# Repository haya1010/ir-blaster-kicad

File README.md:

# M5 / ESP32 High-Power IR Blaster — Rev A

M5 Atom または ESP32 から家電を操作するための、赤外線送受信ボードです。
既存の `m5-ir-remote-studio` の初期設定に合わせ、送信は GPIO26、受信は GPIO32 を想定しています。

## できること

- 940 nm 高出力IR LEDを3灯同時にパルス駆動
- AO3400A MOSFETでESP32のGPIOを保護
- TSOP38238（38 kHz）でリモコン信号を受信
- 受信部を3.3 Vで動かし、ESP32入力へ安全な電圧で返す
- TX動作確認用の可視LED
- JST-PH 4ピンでM5 Atom／ESP32へ接続
- 52 × 40 mm、M3穴4個

## 接続

| J1 pin | 信号 | M5 Atom / ESP32 |
|---|---|---|
| 1 | IR_TX | GPIO26 |
| 2 | IR_RX | GPIO32 |
| 3 | +5V | 5V |
| 4 | GND | GND |

J1のシルク面表記は左から `TX / RX / 5V / GND` です。Groveケーブルは製品により信号線の割り当てが異なるため、色だけで判断せず導通を確認してください。

## 電気的な目安

IR LED 1灯あたりのピーク電流は、5 V、順方向電圧約1.35 V、33 Ωとして約111 mAです。
3灯合計は送信パルス中に約333 mAとなります。38 kHz変調かつ短いリモコン送信を前提としています。

連続点灯はしないでください。IR LEDにはパルス定格に余裕のある部品（TSAL6200相当）を使い、R3〜R5はパルス負荷に耐える0.5 W品を推奨します。

## KiCadで開く

`m5_ir_blaster.kicad_pro` または `m5_ir_blaster.kicad_pcb` を開いてください。
フットプリントはPCBファイル内に埋め込んであるため、追加ライブラリは不要です。

## JLCPCBで基板だけ注文する

アップロードするファイルは `manufacturing/m5_ir_blaster_revA_gerbers.zip` です。
KiCadプロジェクトZIPではなく、Gerber ZIPの方を使ってください。

推奨する初回設定:

| 項目 | 設定 |
|---|---|
| Base Material | FR-4 |
| Layers | 2 |
| Dimensions | 52 × 40 mm（自動認識を確認） |
| PCB Qty | 5 |
| Thickness | 1.6 mm |
| Copper Weight | 1 oz |
| PCB Color | Green（好みで変更可） |
| Silkscreen | White |
| Surface Finish | LeadFree HASL |
| Via Covering | Tented |
| Remove Order Number | 見た目優先なら Yes |
| PCB Assembly | No（部品は手はんだ） |

アップロード後のGerber Viewerで、外形、M3穴4個、IR LED穴3組、J1の4ピン穴、表面シルクを確認してください。

## 製造前の確認

これは試作Rev Aです。発注前に次を確認してください。

1. 使用するJSTコネクタの実物とピン順
2. 選んだIR LEDの極性と最大パルス電流
3. TSOP38238互換品のピン配列（OUT / GND / VS）
4. KiCadのDRC
5. 実機の5 V供給能力

## データシート確認済みの要点

- MCP1700 SOT-23: 1=GND、2=VOUT、3=VIN
- TSOP38238: 1=OUT、2=GND、3=VS
- TSAL6200: 940 nm、連続100 mA、規定条件でピーク200 mA
- AO3400A: 2.5 Vゲート駆動時のオン抵抗が規定されたロジックレベルMOSFET

メーカー資料:

- https://www.microchip.com/en-us/product/mcp1700
- https://www.vishay.com/docs/82491/tsop382.pdf
- https://www.vishay.com/docs/81010/tsal6200.pdf
- https://www.aosmd.com/products/mosfets/low-voltage-mosfets-12v-30v/ao3400a

## ファームウェア

既存スケッチの設定をそのまま使用できます。

```cpp
static const uint16_t IR_RX_PIN = 32;
static const uint16_t IR_TX_PIN = 26;
```

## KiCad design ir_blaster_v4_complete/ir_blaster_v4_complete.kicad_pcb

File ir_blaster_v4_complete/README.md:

# IR Blaster HW V1.0 — REV4 complete

ESP32-WROOM-32E-N16、USB-C 5V入力、12灯IR送信、IR受信、操作ボタン、
試作用1x6書き込み端子、量産用2x3ポゴパッドを載せた直径78 mmの完成基板です。

標準の発注構成は **Hybrid PCBA** です。JLCPCBにはSMT部品だけを実装してもらい、
D1–D12、U_RX、C_BULK、J_PROGはDNP（未実装）にします。これらは後から手はんだします。

## そのまま使う発注ファイル

- `manufacturing/ir_blaster_v4_complete_gerbers.zip`
- `assembly/BOM_JLCPCB.csv`
- `assembly/CPL_JLCPCB.csv`
- 一括確認用 `release/ir_blaster_v4_complete_order_bundle.zip`
- 組立図 `docs/ir_blaster_v4_complete_assembly_drawing.pdf`
- 組立注記 `docs/ASSEMBLY_DRAWING.md`

## 検査結果

- KiCad 9 ERC: blocking error 0
- KiCad 9 DRC: blocking error 0 / unconnected 0
- 2層、FR-4、1.6 mm、1 oz、外形78 x 78 mm
- USB-Cは5 V給電専用。データ線は未接続、CC1/CC2は各5.1 kΩでGNDへ接続
- JLCPCB Gerber Viewerで2層・78 x 78 mmとして解析済み（2026-08-16）

発注操作の直前に `docs/PRE_ORDER_CHECKLIST.md` とJLCPCBの部品向きプレビューを確認してください。

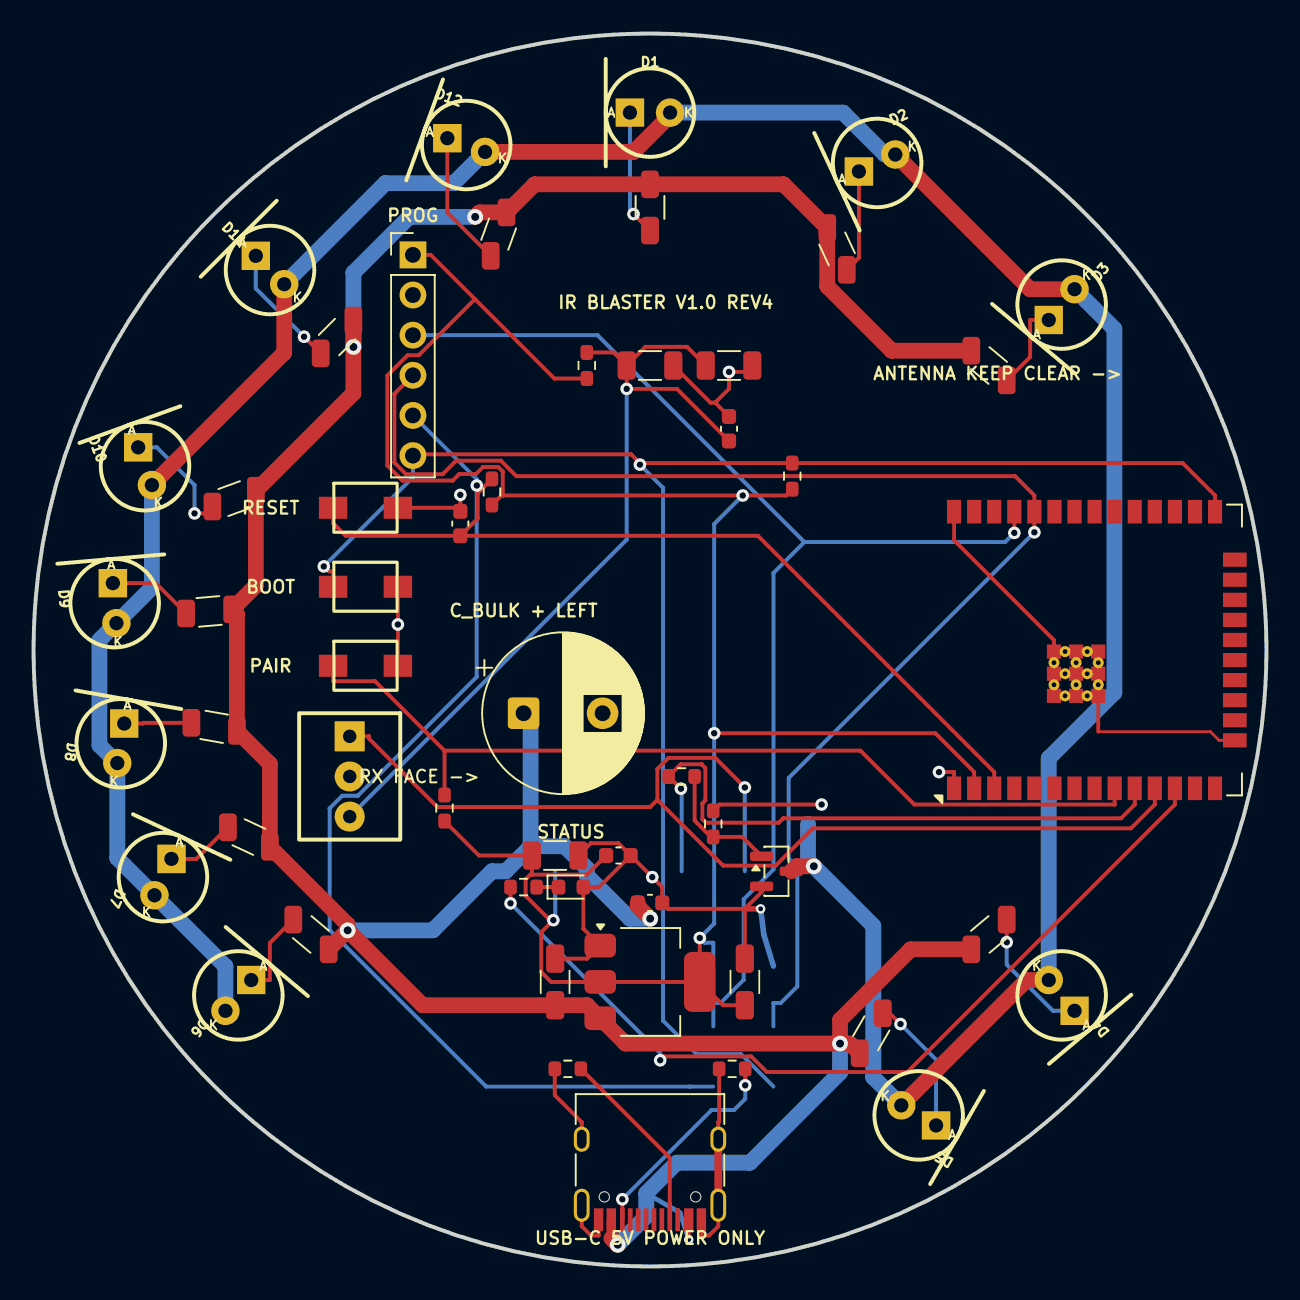
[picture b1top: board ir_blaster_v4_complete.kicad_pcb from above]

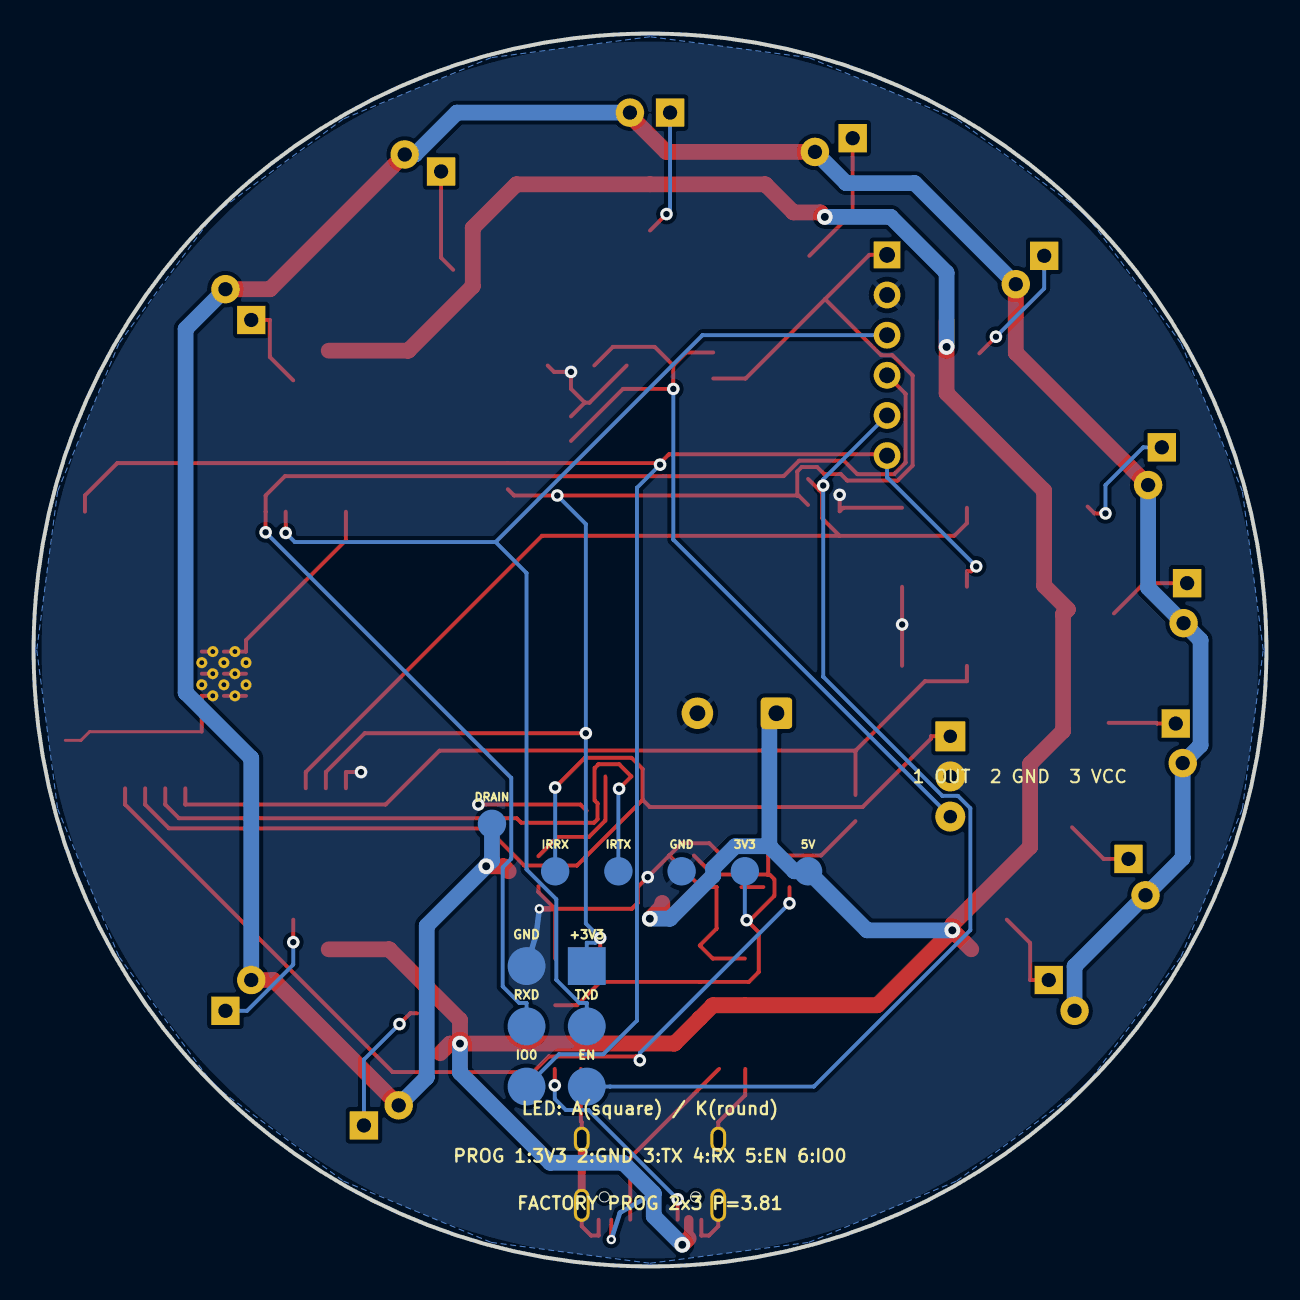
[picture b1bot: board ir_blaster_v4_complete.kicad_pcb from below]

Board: 2 copper layers, 78.0 x 78.0 mm, 65 parts (12 on the bottom side), 29 nets.

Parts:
C1, C2, C4: 22uF; C_1206_3216Metric
C3, C5: 100nF; C_0603_1608Metric
C_BULK: 1000uF 10V DNP; CP_Radial_D10.0mm_P5.00mm
C_EN: 1uF; C_0603_1608Metric
C_RX1, C_RX2: 22uF; C_1206_3216Metric
C_RX3: 100nF; C_0603_1608Metric
D1, D4, D7, D10: OSI5LA7WA1B_WIDE_DNP; IR_LED_5mm_Universal_P2.54
D2, D3, D5, D6, D8, D9, D11, D12: OSI5LA5A33A-B_NARROW_DNP; IR_LED_5mm_Universal_P2.54
D_STATUS: RED; LED_0603_1608Metric
J1: USB-C 5V POWER ONLY; USB_C_Receptacle_HRO_TYPE-C-31-M-12
J_PROG: 1x6 2.54mm DNP; PinHeader_1x06_P2.54mm_Vertical
Q1: AO3400A; SOT-23
R1, R2, R3, R4, R5, R6, R7, R8, R9, R10, R11, R12: 100R 0.25W; R_1206_3216Metric
R_BOOT: 10k; R_0603_1608Metric
R_CC1, R_CC2: 5.1k; R_0603_1608Metric
R_EN: 10k; R_0603_1608Metric
R_GATE: 220R; R_0603_1608Metric
R_PAIR: 10k; R_0603_1608Metric
R_PD: 10k; R_0603_1608Metric
R_RX: 100R; R_0603_1608Metric
R_STATUS: 1k; R_0603_1608Metric
SW_BOOT: TS-1088R-02026
SW_PAIR: TS-1088R-02026
SW_RESET: TS-1088R-02026
TP_3V3: 3V3; TestPad_D1.8
TP_5V: 5V; TestPad_D1.8
TP_DRAIN: DRAIN; TestPad_D1.8
TP_GND: GND; TestPad_D1.8
TP_PROG_3V3: +3V3; PogoPad_D2.4
TP_PROG_EN: EN; PogoPad_D2.4
TP_PROG_GND: GND; PogoPad_D2.4
TP_PROG_IO0: IO0; PogoPad_D2.4
TP_PROG_RXD: RXD; PogoPad_D2.4
TP_PROG_TXD: TXD; PogoPad_D2.4
TP_RX: IRRX; TestPad_D1.8
TP_TX: IRTX; TestPad_D1.8
U1: ESP32-WROOM-32E-N16; ESP32-WROOM-32E
U2: AMS1117-3.3; SOT-223-3_TabPin2
U_RX: OSRB38C9AA_DNP; OSRB38C9AA

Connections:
+3V3: C2.1, C4.1, C5.1, J_PROG.1, R_BOOT.1, R_EN.1, R_PAIR.1, R_RX.1, TP_3V3.1, TP_PROG_3V3.1, U1.2, U2.2
+5V: C1.1, C3.1, C_BULK.1, J1.A4, J1.A9, J1.B4, J1.B9, R1.1, R2.1, R3.1, R4.1, R5.1, R6.1, R7.1, R8.1, R9.1, R10.1, R11.1, R12.1, TP_5V.1, U2.3
CC1: J1.A5, R_CC1.1
CC2: J1.B5, R_CC2.1
EN: C_EN.1, J_PROG.5, R_EN.2, SW_RESET.1, TP_PROG_EN.1, U1.3
GND: C1.2, C2.2, C3.2, C4.2, C5.2, C_BULK.2, C_EN.2, C_RX1.2, C_RX2.2, C_RX3.2, D_STATUS.2, J1.A1, J1.A12, J1.B1, J1.B12, J1.S1, J_PROG.2, Q1.2, R_CC1.2, R_CC2.2, R_PD.2, SW_BOOT.2, SW_PAIR.2, SW_RESET.2, TP_GND.1, TP_PROG_GND.1, U1.1, U1.15, U1.38, U1.39, U2.1, U_RX.2
IO0: J_PROG.6, R_BOOT.2, SW_BOOT.1, TP_PROG_IO0.1, U1.25
IR_RX: TP_RX.1, U1.11, U_RX.1
IR_RX_VCC: C_RX1.1, C_RX2.1, C_RX3.1, R_RX.2, U_RX.3
IR_TX: R_GATE.1, TP_TX.1, U1.10
LED_A1: D1.1, R1.2
LED_A2: D2.1, R2.2
LED_A3: D3.1, R3.2
LED_A4: D4.1, R4.2
LED_A5: D5.1, R5.2
LED_A6: D6.1, R6.2
LED_A7: D7.1, R7.2
LED_A8: D8.1, R8.2
LED_A9: D9.1, R9.2
LED_A10: D10.1, R10.2
LED_A11: D11.1, R11.2
LED_A12: D12.1, R12.2
LED_DRAIN: D1.2, D2.2, D3.2, D4.2, D5.2, D6.2, D7.2, D8.2, D9.2, D10.2, D11.2, D12.2, Q1.3, TP_DRAIN.1
MOS_GATE: Q1.1, R_GATE.2, R_PD.1
PAIR: R_PAIR.2, SW_PAIR.1, U1.9
STATUS: R_STATUS.1, U1.12
STATUS_LED: D_STATUS.1, R_STATUS.2
U0RXD: J_PROG.4, TP_PROG_RXD.1, U1.34
U0TXD: J_PROG.3, TP_PROG_TXD.1, U1.35

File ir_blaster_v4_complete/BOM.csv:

Reference,Qty,Value,Footprint,Manufacturer,MPN,JLC/LCSC,Assembly,Notes
D1,1,OSI5LA7WA1B_WIDE_DNP,IR_LED_5mm_Universal_P2.54,OptoSupply,OSI5LA7WA1B,DNP,DNP / hand solder,Tilt 30-45 degrees outward by hand
R1,1,100R 0.25W,R_1206_3216Metric,UNI-ROYAL,1206W4F1000T5E,C17901,SMT,
D2,1,OSI5LA5A33A-B_NARROW_DNP,IR_LED_5mm_Universal_P2.54,OptoSupply,OSI5LA5A33A-B,DNP,DNP / hand solder,Tilt 30-45 degrees outward by hand
R2,1,100R 0.25W,R_1206_3216Metric,UNI-ROYAL,1206W4F1000T5E,C17901,SMT,
D3,1,OSI5LA5A33A-B_NARROW_DNP,IR_LED_5mm_Universal_P2.54,OptoSupply,OSI5LA5A33A-B,DNP,DNP / hand solder,Tilt 30-45 degrees outward by hand
R3,1,100R 0.25W,R_1206_3216Metric,UNI-ROYAL,1206W4F1000T5E,C17901,SMT,
D4,1,OSI5LA7WA1B_WIDE_DNP,IR_LED_5mm_Universal_P2.54,OptoSupply,OSI5LA7WA1B,DNP,DNP / hand solder,Tilt 30-45 degrees outward by hand
R4,1,100R 0.25W,R_1206_3216Metric,UNI-ROYAL,1206W4F1000T5E,C17901,SMT,
D5,1,OSI5LA5A33A-B_NARROW_DNP,IR_LED_5mm_Universal_P2.54,OptoSupply,OSI5LA5A33A-B,DNP,DNP / hand solder,Tilt 30-45 degrees outward by hand
R5,1,100R 0.25W,R_1206_3216Metric,UNI-ROYAL,1206W4F1000T5E,C17901,SMT,
D6,1,OSI5LA5A33A-B_NARROW_DNP,IR_LED_5mm_Universal_P2.54,OptoSupply,OSI5LA5A33A-B,DNP,DNP / hand solder,Tilt 30-45 degrees outward by hand
R6,1,100R 0.25W,R_1206_3216Metric,UNI-ROYAL,1206W4F1000T5E,C17901,SMT,
D7,1,OSI5LA7WA1B_WIDE_DNP,IR_LED_5mm_Universal_P2.54,OptoSupply,OSI5LA7WA1B,DNP,DNP / hand solder,Tilt 30-45 degrees outward by hand
R7,1,100R 0.25W,R_1206_3216Metric,UNI-ROYAL,1206W4F1000T5E,C17901,SMT,
D8,1,OSI5LA5A33A-B_NARROW_DNP,IR_LED_5mm_Universal_P2.54,OptoSupply,OSI5LA5A33A-B,DNP,DNP / hand solder,Tilt 30-45 degrees outward by hand
R8,1,100R 0.25W,R_1206_3216Metric,UNI-ROYAL,1206W4F1000T5E,C17901,SMT,
D9,1,OSI5LA5A33A-B_NARROW_DNP,IR_LED_5mm_Universal_P2.54,OptoSupply,OSI5LA5A33A-B,DNP,DNP / hand solder,Tilt 30-45 degrees outward by hand
R9,1,100R 0.25W,R_1206_3216Metric,UNI-ROYAL,1206W4F1000T5E,C17901,SMT,
D10,1,OSI5LA7WA1B_WIDE_DNP,IR_LED_5mm_Universal_P2.54,OptoSupply,OSI5LA7WA1B,DNP,DNP / hand solder,Tilt 30-45 degrees outward by hand
R10,1,100R 0.25W,R_1206_3216Metric,UNI-ROYAL,1206W4F1000T5E,C17901,SMT,
D11,1,OSI5LA5A33A-B_NARROW_DNP,IR_LED_5mm_Universal_P2.54,OptoSupply,OSI5LA5A33A-B,DNP,DNP / hand solder,Tilt 30-45 degrees outward by hand
R11,1,100R 0.25W,R_1206_3216Metric,UNI-ROYAL,1206W4F1000T5E,C17901,SMT,
D12,1,OSI5LA5A33A-B_NARROW_DNP,IR_LED_5mm_Universal_P2.54,OptoSupply,OSI5LA5A33A-B,DNP,DNP / hand solder,Tilt 30-45 degrees outward by hand
R12,1,100R 0.25W,R_1206_3216Metric,UNI-ROYAL,1206W4F1000T5E,C17901,SMT,
U1,1,ESP32-WROOM-32E-N16,ESP32-WROOM-32E,Espressif Systems,ESP32-WROOM-32E-N16,C701343,SMT,16MB flash; Standard PCBA; X-ray required
J1,1,USB-C 5V POWER ONLY,USB_C_Receptacle_HRO_TYPE-C-31-M-12,Korean Hroparts Elec,TYPE-C-31-M-12,C165948,SMT,
U2,1,AMS1117-3.3,SOT-223-3_TabPin2,Advanced Monolithic Systems,AMS1117-3.3,C6186,SMT,1A LDO; large copper area required
C1,1,22uF,C_1206_3216Metric,Samsung Electro-Mechanics,CL31A226KAHNNNE,C12891,SMT,
C2,1,22uF,C_1206_3216Metric,Samsung Electro-Mechanics,CL31A226KAHNNNE,C12891,SMT,
C3,1,100nF,C_0603_1608Metric,Samsung Electro-Mechanics,CL10B104KB8NNNC,C1591,SMT,
C4,1,22uF,C_1206_3216Metric,Samsung Electro-Mechanics,CL31A226KAHNNNE,C12891,SMT,
C5,1,100nF,C_0603_1608Metric,Samsung Electro-Mechanics,CL10B104KB8NNNC,C1591,SMT,
R_EN,1,10k,R_0603_1608Metric,UNI-ROYAL,0603WAF1002T5E,C25804,SMT,
C_EN,1,1uF,C_0603_1608Metric,Samsung Electro-Mechanics,CL10A105KB8NNNC,C15849,SMT,
R_BOOT,1,10k,R_0603_1608Metric,UNI-ROYAL,0603WAF1002T5E,C25804,SMT,
SW_RESET,1,TS-1088R-02026,TS-1088R-02026,XUNPU,TS-1088R-02026,C455280,SMT,
SW_BOOT,1,TS-1088R-02026,TS-1088R-02026,XUNPU,TS-1088R-02026,C455280,SMT,
SW_PAIR,1,TS-1088R-02026,TS-1088R-02026,XUNPU,TS-1088R-02026,C455280,SMT,
R_PAIR,1,10k,R_0603_1608Metric,UNI-ROYAL,0603WAF1002T5E,C25804,SMT,
R_GATE,1,220R,R_0603_1608Metric,UNI-ROYAL,0603WAF2200T5E,C22962,SMT,
R_PD,1,10k,R_0603_1608Metric,UNI-ROYAL,0603WAF1002T5E,C25804,SMT,
Q1,1,AO3400A,SOT-23,Alpha & Omega Semiconductor,AO3400A,C20917,SMT,
R_RX,1,100R,R_0603_1608Metric,UNI-ROYAL,0603WAF1000T5E,C22775,SMT,
C_RX1,1,22uF,C_1206_3216Metric,Samsung Electro-Mechanics,CL31A226KAHNNNE,C12891,SMT,
C_RX2,1,22uF,C_1206_3216Metric,Samsung Electro-Mechanics,CL31A226KAHNNNE,C12891,SMT,
C_RX3,1,100nF,C_0603_1608Metric,Samsung Electro-Mechanics,CL10B104KB8NNNC,C1591,SMT,
U_RX,1,OSRB38C9AA,OSRB38C9AA,OptoSupply,OSRB38C9AA,DNP,DNP / hand solder,
R_STATUS,1,1k,R_0603_1608Metric,UNI-ROYAL,0603WAF1001T5E,C21190,SMT,
D_STATUS,1,RED,LED_0603_1608Metric,Hubei KENTO,KT-0603R,C2286,SMT,
C_BULK,1,1000uF 10V DNP,CP_Radial_D10.0mm_P5.00mm,User selected,1000uF 10V radial,DNP,DNP / hand solder,Observe + and - silkscreen
J_PROG,1,1x6 2.54mm DNP,PinHeader_1x06_P2.54mm_Vertical,Generic,2.54mm male header,DNP,DNP / hand solder,
R_CC1,1,5.1k,R_0603_1608Metric,UNI-ROYAL,0603WAF5101T5E,C23186,SMT,
R_CC2,1,5.1k,R_0603_1608Metric,UNI-ROYAL,0603WAF5101T5E,C23186,SMT,

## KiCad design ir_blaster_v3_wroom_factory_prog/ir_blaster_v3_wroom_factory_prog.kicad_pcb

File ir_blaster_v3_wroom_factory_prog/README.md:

# IR Blaster V3 — WROOM Factory Programming Interface

This is a separate KiCad revision. It does not overwrite `ir_blaster_v1` or
`ir_blaster_v2_smd`.

## Scope

This revision implements the section-8 programming interface milestone:

- ESP32-WROOM-32E-N16 footprint and UART0 programming nets
- bottom-side six-pad factory pogo interface
- separate 2.54 mm 1x6 prototype header, marked DNP
- pin-1 and per-signal silkscreen labels
- JLCPCB BOM/CPL and fabrication outputs
- safe programming instructions

It is an integration milestone, not yet the complete standalone product. USB-C,
the regulator, IR LED drivers, IR receiver, bulk capacitor, buttons and final
case/3D interference checks still need to be merged from the master specification
before a production order.

## Pinout

| Pin | Net | Board label |
|---:|---|---|
| 1 | +3V3 | 3V3 |
| 2 | GND | GND |
| 3 | ESP32 TXD0 | TX |
| 4 | ESP32 RXD0 | RX |
| 5 | EN | EN |
| 6 | IO0 | IO0 |

The bottom pogo pads use the same order in a straight 1x6 array at 3.81 mm
pitch. Pad diameter is 2.4 mm and pad 1 is rectangular.

## Verification status

- PCB DRC: 0 electrical errors, 0 unconnected pads
- Schematic ERC: 0 violations
- Remaining DRC warnings: embedded custom pogo footprint library entries and
  the intentional WROOM footprint change described below

The official KiCad `ESP32-WROOM-32E` land pattern is used. Its 0.20 mm exposed-
pad thermal-via drills were enlarged to 0.30 mm with 0.70 mm pads to fit the
normal JLCPCB manufacturing capability/cost class. This intentional difference
is why KiCad reports a library mismatch warning for U1.

## Manufacturing files

- `manufacturing/gerbers/`: Gerber and drill files
- `manufacturing/ir_blaster_v3_wroom_factory_prog_gerbers.zip`: PCB upload ZIP
- `assembly/BOM_JLCPCB.csv`: assembled parts only
- `assembly/CPL_JLCPCB.csv`: placement data
- `BOM.csv`: engineering BOM including DNP items

`J_PROG` and all pogo pads are PCB-only/DNP and are excluded from the JLCPCB
production BOM and placement file.

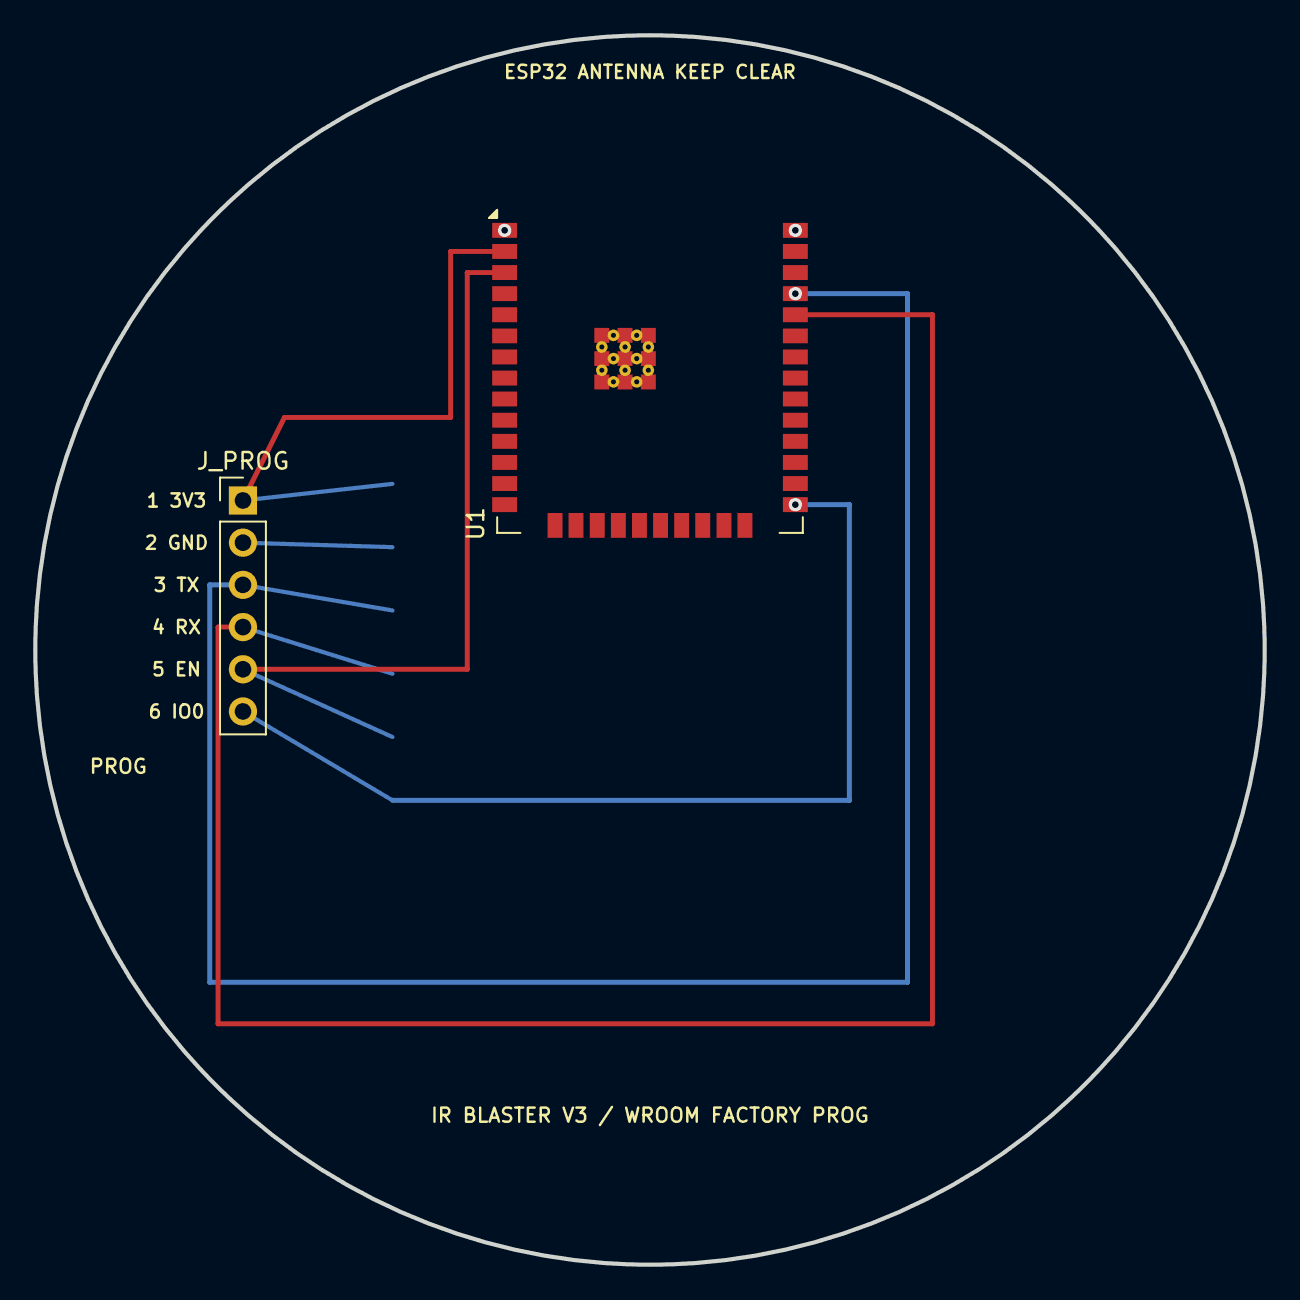
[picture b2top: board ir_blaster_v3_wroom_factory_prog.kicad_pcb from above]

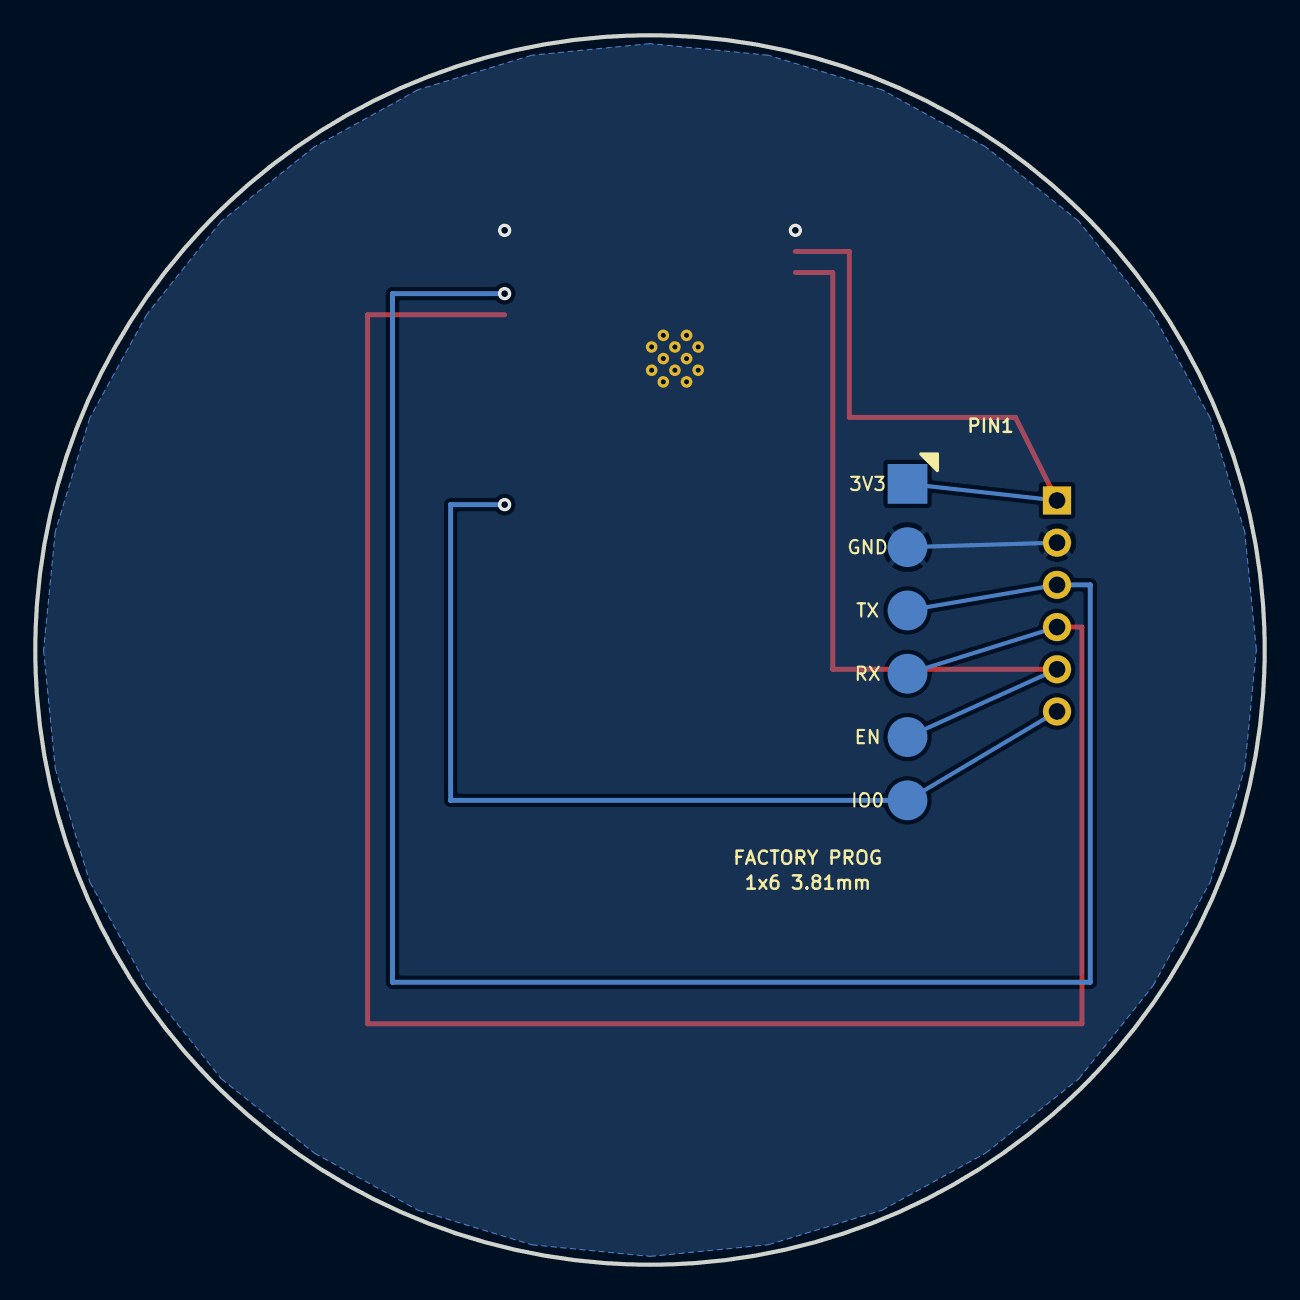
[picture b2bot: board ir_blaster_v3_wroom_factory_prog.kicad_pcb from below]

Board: 2 copper layers, 74.0 x 74.0 mm, 8 parts (6 on the bottom side), 6 nets.

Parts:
J_PROG: PinHeader_1x06_P2.54mm_Vertical_DNP; PinHeader_1x06_P2.54mm_Vertical
TP_PROG_3V3: 3V3; PogoPad_D2.4mm
TP_PROG_EN: EN; PogoPad_D2.4mm
TP_PROG_GND: GND; PogoPad_D2.4mm
TP_PROG_IO0: IO0; PogoPad_D2.4mm
TP_PROG_RX: RX; PogoPad_D2.4mm
TP_PROG_TX: TX; PogoPad_D2.4mm
U1: ESP32-WROOM-32E-N16; ESP32-WROOM-32E

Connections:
+3V3: J_PROG.1, TP_PROG_3V3.1, U1.2
EN: J_PROG.5, TP_PROG_EN.1, U1.3
GND: J_PROG.2, TP_PROG_GND.1, U1.1, U1.38, U1.39
IO0: J_PROG.6, TP_PROG_IO0.1, U1.25
U0RXD: J_PROG.4, TP_PROG_RX.1, U1.34
U0TXD: J_PROG.3, TP_PROG_TX.1, U1.35

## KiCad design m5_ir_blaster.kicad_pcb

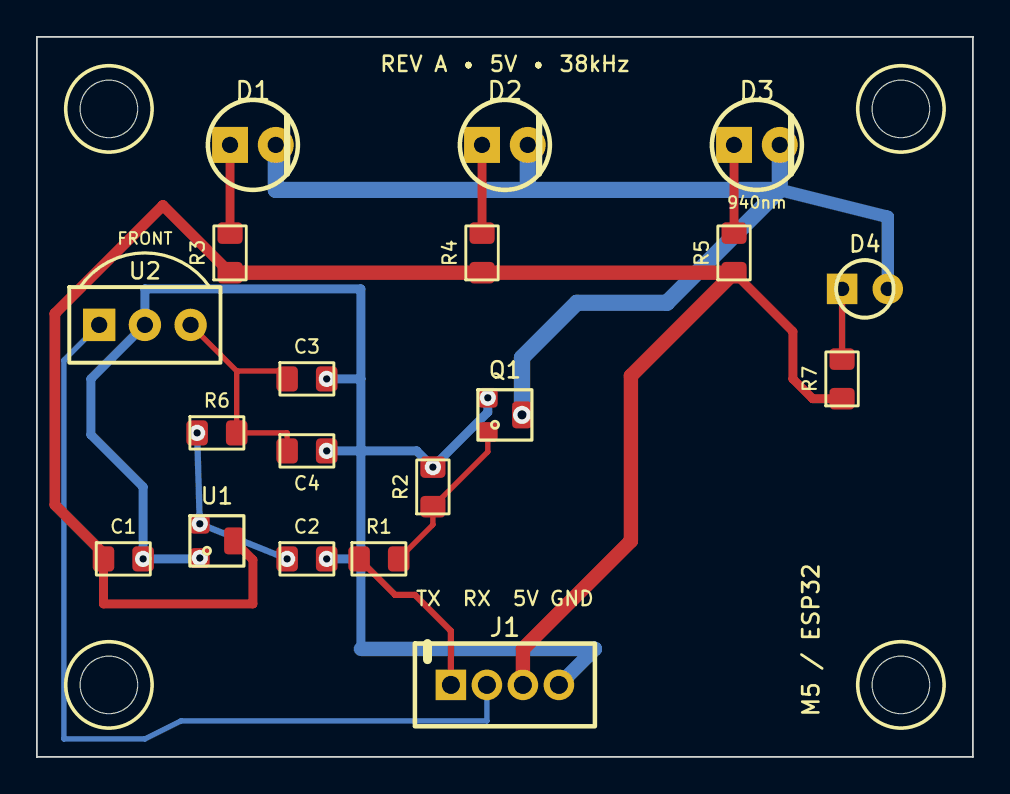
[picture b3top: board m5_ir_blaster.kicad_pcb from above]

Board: 2 copper layers, 52.0 x 40.0 mm, 23 parts (0 on the bottom side), 12 nets.

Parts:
C1, C2: 1uF; C_0805
C3: 4.7uF; C_0805
C4: 100nF; C_0805
D1, D2, D3: IR_LED_940nm; LED_D5.0mm_IR
D4: TX_VISIBLE; LED_D3.0mm
H1, H2, H3, H4: M3; MountingHole_3.2mm_M3
J1: GROVE_M5_PORT; JST_PH_1x04_P2.00mm_Vertical
Q1: AO3400A; SOT-23
R1, R6: 100R; R_0805
R2: 100k; R_0805
R3, R4, R5: 33R; R_0805
R7: 1k; R_0805
U1: MCP1700-3302; SOT-23
U2: TSOP38238; TSOP_3pin_P2.54

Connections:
+3V3: C2.1, R6.1, U1.2
+5V: C1.1, J1.3, R3.1, R4.1, R5.1, R7.1, U1.3
GATE: Q1.1, R1.2, R2.1
GND: C1.2, C2.2, C3.2, C4.2, J1.4, Q1.2, R2.2, U1.1, U2.2
IR_RX: J1.2, U2.1
IR_SINK: D1.2, D2.2, D3.2, D4.2, Q1.3
IR_TX: J1.1, R1.1
LED1_A: D1.1, R3.2
LED2_A: D2.1, R4.2
LED3_A: D3.1, R5.2
RX_VCC: C3.1, C4.1, R6.2, U2.3
STATUS_A: D4.1, R7.2

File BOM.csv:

Reference,Qty,Value,Description,Footprint / notes
J1,1,JST-PH 4-pin,Grove/M5 cable connector,2.00 mm vertical
D1 D2 D3,3,940 nm IR LED,High-output 5 mm IR emitter,Vishay TSAL6200 or equivalent
D4,1,Visible LED,TX activity indicator,3 mm through-hole
R1,1,100 ohm,MOSFET gate resistor,0805
R2,1,100 kohm,MOSFET gate pull-down,0805
R3 R4 R5,3,33 ohm,IR LED current limiting 0.5 W pulse-rated,0805 high-power
R6,1,100 ohm,IR receiver supply filter,0805
R7,1,1 kohm,Visible LED current limiting,0805
Q1,1,AO3400A,N-channel logic-level MOSFET,SOT-23
U1,1,MCP1700-3302,3.3 V LDO regulator,SOT-23
U2,1,TSOP38238,38 kHz IR receiver,Through-hole 3-pin 2.54 mm
C1 C2,2,1 uF 10 V,LDO input/output capacitors,0805 X7R
C3,1,4.7 uF 10 V,IR receiver supply filter,0805 X7R
C4,1,100 nF,IR receiver local bypass,0805 X7R
H1 H2 H3 H4,4,M3 mounting hole,NPTH,3.2 mm drill

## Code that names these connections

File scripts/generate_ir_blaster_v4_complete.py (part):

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    ]

    # Receiver filter capacitors to the filtered rail and ground.
    # Their pin-1 pads lie on IR_RX_VCC; stitch the local rail with a short chain.
    rx_filter_points = [r_rx["2"]] + [cap["1"] for cap in rx_caps]
    for a, b in zip(rx_filter_points, rx_filter_points[1:]):
        tracks.append(segment(a, b, "IR_RX_VCC", 0.4))
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    notes = [
        ("IR BLASTER HW V1.0 / REV4 - COMPLETE STANDALONE PRODUCT", 20, 245, 1.5),
        ("USB-C is 5V POWER ONLY. CC1/CC2 each use 5.1k Rd to GND.", 20, 251, 0.9),
        ("U1: ESP32-WROOM-32E-N16. GPIO25=IR_TX, GPIO26=IR_RX, GPIO27=STATUS, GPIO33=PAIR.", 20, 256, 0.9),
        ("Q1 AO3400A mapping: pin1=G, pin2=S, pin3=D. D1..D12 mapping: pin1=A, pin2=K.", 20, 261, 0.9),
        ("HYBRID BUILD: D1-D12, U_RX, C_BULK and J_PROG are DNP/user soldered.", 20, 266, 0.9),
    ]
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
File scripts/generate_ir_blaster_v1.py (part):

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    pads = []
    for i, name in enumerate(names, 1):
        net = None
        if left and name == "GPIO25": net = (4, "IR_TX")
        elif left and name == "5V": net = (1, "+5V")
        elif left and name == "GND": net = (2, "GND")
        net_s = f' (net {net[0]} "{net[1]}")' if net else ""
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    for i in range(12):
        y = 38 + i * 7.5
        items += [text(f"+5V -> R{i+1} 100R -> D{i+1} anode; D{i+1} cathode -> LED_DRAIN", 25, y, 0.9)]
    items += [text("LED_DRAIN -> Q1 pin 2 DRAIN; Q1 pin 1 SOURCE -> GND", 25, 132, 0.95)]
    items += [text("GPIO25 / IR_TX -> RG 220R -> Q1 pin 3 GATE", 25, 140, 0.95)]
    items += [text("RPD 10k: GATE -> GND", 25, 148, 0.95), text("Cbulk 1000uF + Cdec 100nF: +5V -> GND", 25, 156, 0.95)]
    items += [text("D1,D4,D7,D10 = OSI5LA7WA1B wide 100°; remaining LEDs = OSI5LA5A33A-B narrow 30°", 25, 166, 0.85)]
    items += [text("Confirmed mapping: both LED types pin 1=A, pin 2=K; Q1 pin 1=S, pin 2=D, pin 3=G", 25, 174, 0.85)]
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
